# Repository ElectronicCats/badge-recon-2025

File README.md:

# REcon Badge 2025

This is the official repository of the REcon Badge 2025. Here you will find the source code for the badge, as well as the documentation and instructions to build it.

## Getting Started

Your badge comes with a pre-installed firmware, but in case you want to reprogram it, you can follow these steps:

1. Download the latest `firmware.uf2` file from the [releases](https://github.com/ElectronicCats/badge-recon-2025/releases/latest) page.

2. Connect the badge to your computer using a USB-C cable.

3. Press and hold the button on the badge while connecting it to the USB port. This will put the badge in bootloader mode.

4. Once the badge is connected, it will appear as a USB drive named `RPI-RP2`. Copy the `firmware.uf2` file to the root of the drive.

5. After copying the file, the badge will automatically reboot and start running the new firmware.

> **Note:** Sometimes you may need to press the reset button on the badge after copying the firmware file to ensure it starts correctly.

### Building the Firmware

To build the firmware from source, you will need to have [Docker](https://www.docker.com/) installed on your machine. Once you have Docker set up, you can follow these steps:

1. Clone the repository:

Using HTTPS:

```bash
git clone https://github.com/ElectronicCats/badge-recon-2025.git
```

Using SSH:

```bash
git clone git@github.com:ElectronicCats/badge-recon-2025.git
```

2. Navigate to the firmware directory:

```bash
cd badge-recon-2025/firmware
```

3. Build the firmware using Docker:

```bash
./build.sh
```

This script will create a `firmware.ino.uf2` file in the `firmware/build` directory.

> To flash the firmware to the badge, follow the same steps as mentioned in the "Getting Started" section, but use the newly built `firmware.ino.uf2` file instead of the pre-built one.

> If you find any issues, please open an issue on the GitHub repository.

## User guide

Your badge comes with an SSD1306 OLED display and 4 buttons for navigation. When you power on the badge, it will display a welcome screen and then show the main menu after you press any button.

All the available applications are listed in the following diagram:

```mermaid
flowchart TD
    Start([Power On]) --> Init[Initialize Hardware]
    Init --> Welcome[Welcome Screen]
    Welcome --> MainMenu[Main Menu]
    
    MainMenu --> Apps[Apps]
    MainMenu --> About[About Screen]
    
    Apps --> NFCMenu[NFC Menu]
    Apps --> MagspoofMenu[Magspoof Menu]
    
    %% NFC Menu items
    NFCMenu --> DetectTags[Detect Tags]
    NFCMenu --> DetectReaders[Detect Readers]
    NFCMenu --> ReadBlock[Read Block]
    NFCMenu --> WriteBlock[Write Block]
    
    %% Magspoof Menu items
    MagspoofMenu --> Emulate[Emulate]
    MagspoofMenu --> Setup[Setup]
    MagspoofMenu --> Help[Help]
    
    %% NFC operations
    DetectTags --> SetReaderMode[Set Reader Mode]
    SetReaderMode --> TagDetection{Tag Detected?}
    TagDetection -->|Yes| DisplayTagInfo[Display Tag Info]
    TagDetection -->|No| BackPressed{Back Pressed?}
    BackPressed -->|Yes| NFCMenu
    BackPressed -->|No| TagDetection
    DisplayTagInfo --> WaitForRemoval[Wait For Tag Removal]
    WaitForRemoval --> BackToMenu[Wait For Back Button]
    BackToMenu --> NFCMenu
    
    %% Magspoof operations
    Setup --> SerialPrompt[Serial Prompt for Tracks]
    SerialPrompt --> InputTracks[Input Track Data]
    InputTracks --> TracksUpdated[Tracks Updated]
    TracksUpdated --> MagspoofMenu
    
    %% Input controller
    subgraph InputControl [Input Controller]
        UpButton[Up Button]
        DownButton[Down Button]
        SelectButton[Select Button]
        BackButton[Back Button]
    end
    
    %% Easter egg
    UpButton --> KonamiCheck{Konami Code?}
    KonamiCheck -->|Yes| EasterEgg[Easter Egg hint]
    KonamiCheck -->|No| MainMenu
```

### NFC Applications

- **Read Block** and **Write Block** applications are the same as **Detect Tags**, but they perform read and read/write operations if the detected tag is a Mifare Classic tag.
- **Detect Readers** allows you to detect NFC readers by emulating a tag.

### Magspoof Application

The **Magspoof** application allows you to emulate a magnetic stripe card.

- You can set up the tracks by entering the data through the serial prompt, use 9600 baud rate to communicate with the badge.
- The **Emulate** option allows you to emulate the magnetic stripe card with the configured tracks.

### Easter Egg

You can get a hint about the Easter egg by pressing the Konami code while the badge shows the REcon logo. The Konami code is:

```
Up, Up, Down, Down, Left, Right, Left, Right
```

## License

Electronic Cats invests time and resources providing this open source design, please support Electronic Cats and open-source hardware by purchasing products from Electronic Cats!

Designed by Electronic Cats.

Firmware released under an GNU AGPL v3.0 license. See the LICENSE file for more information.

Hardware released under an CERN Open Hardware Licence v1.2. See the LICENSE_HARDWARE file for more information.

Electronic Cats is a registered trademark, please do not use if you sell these PCBs.

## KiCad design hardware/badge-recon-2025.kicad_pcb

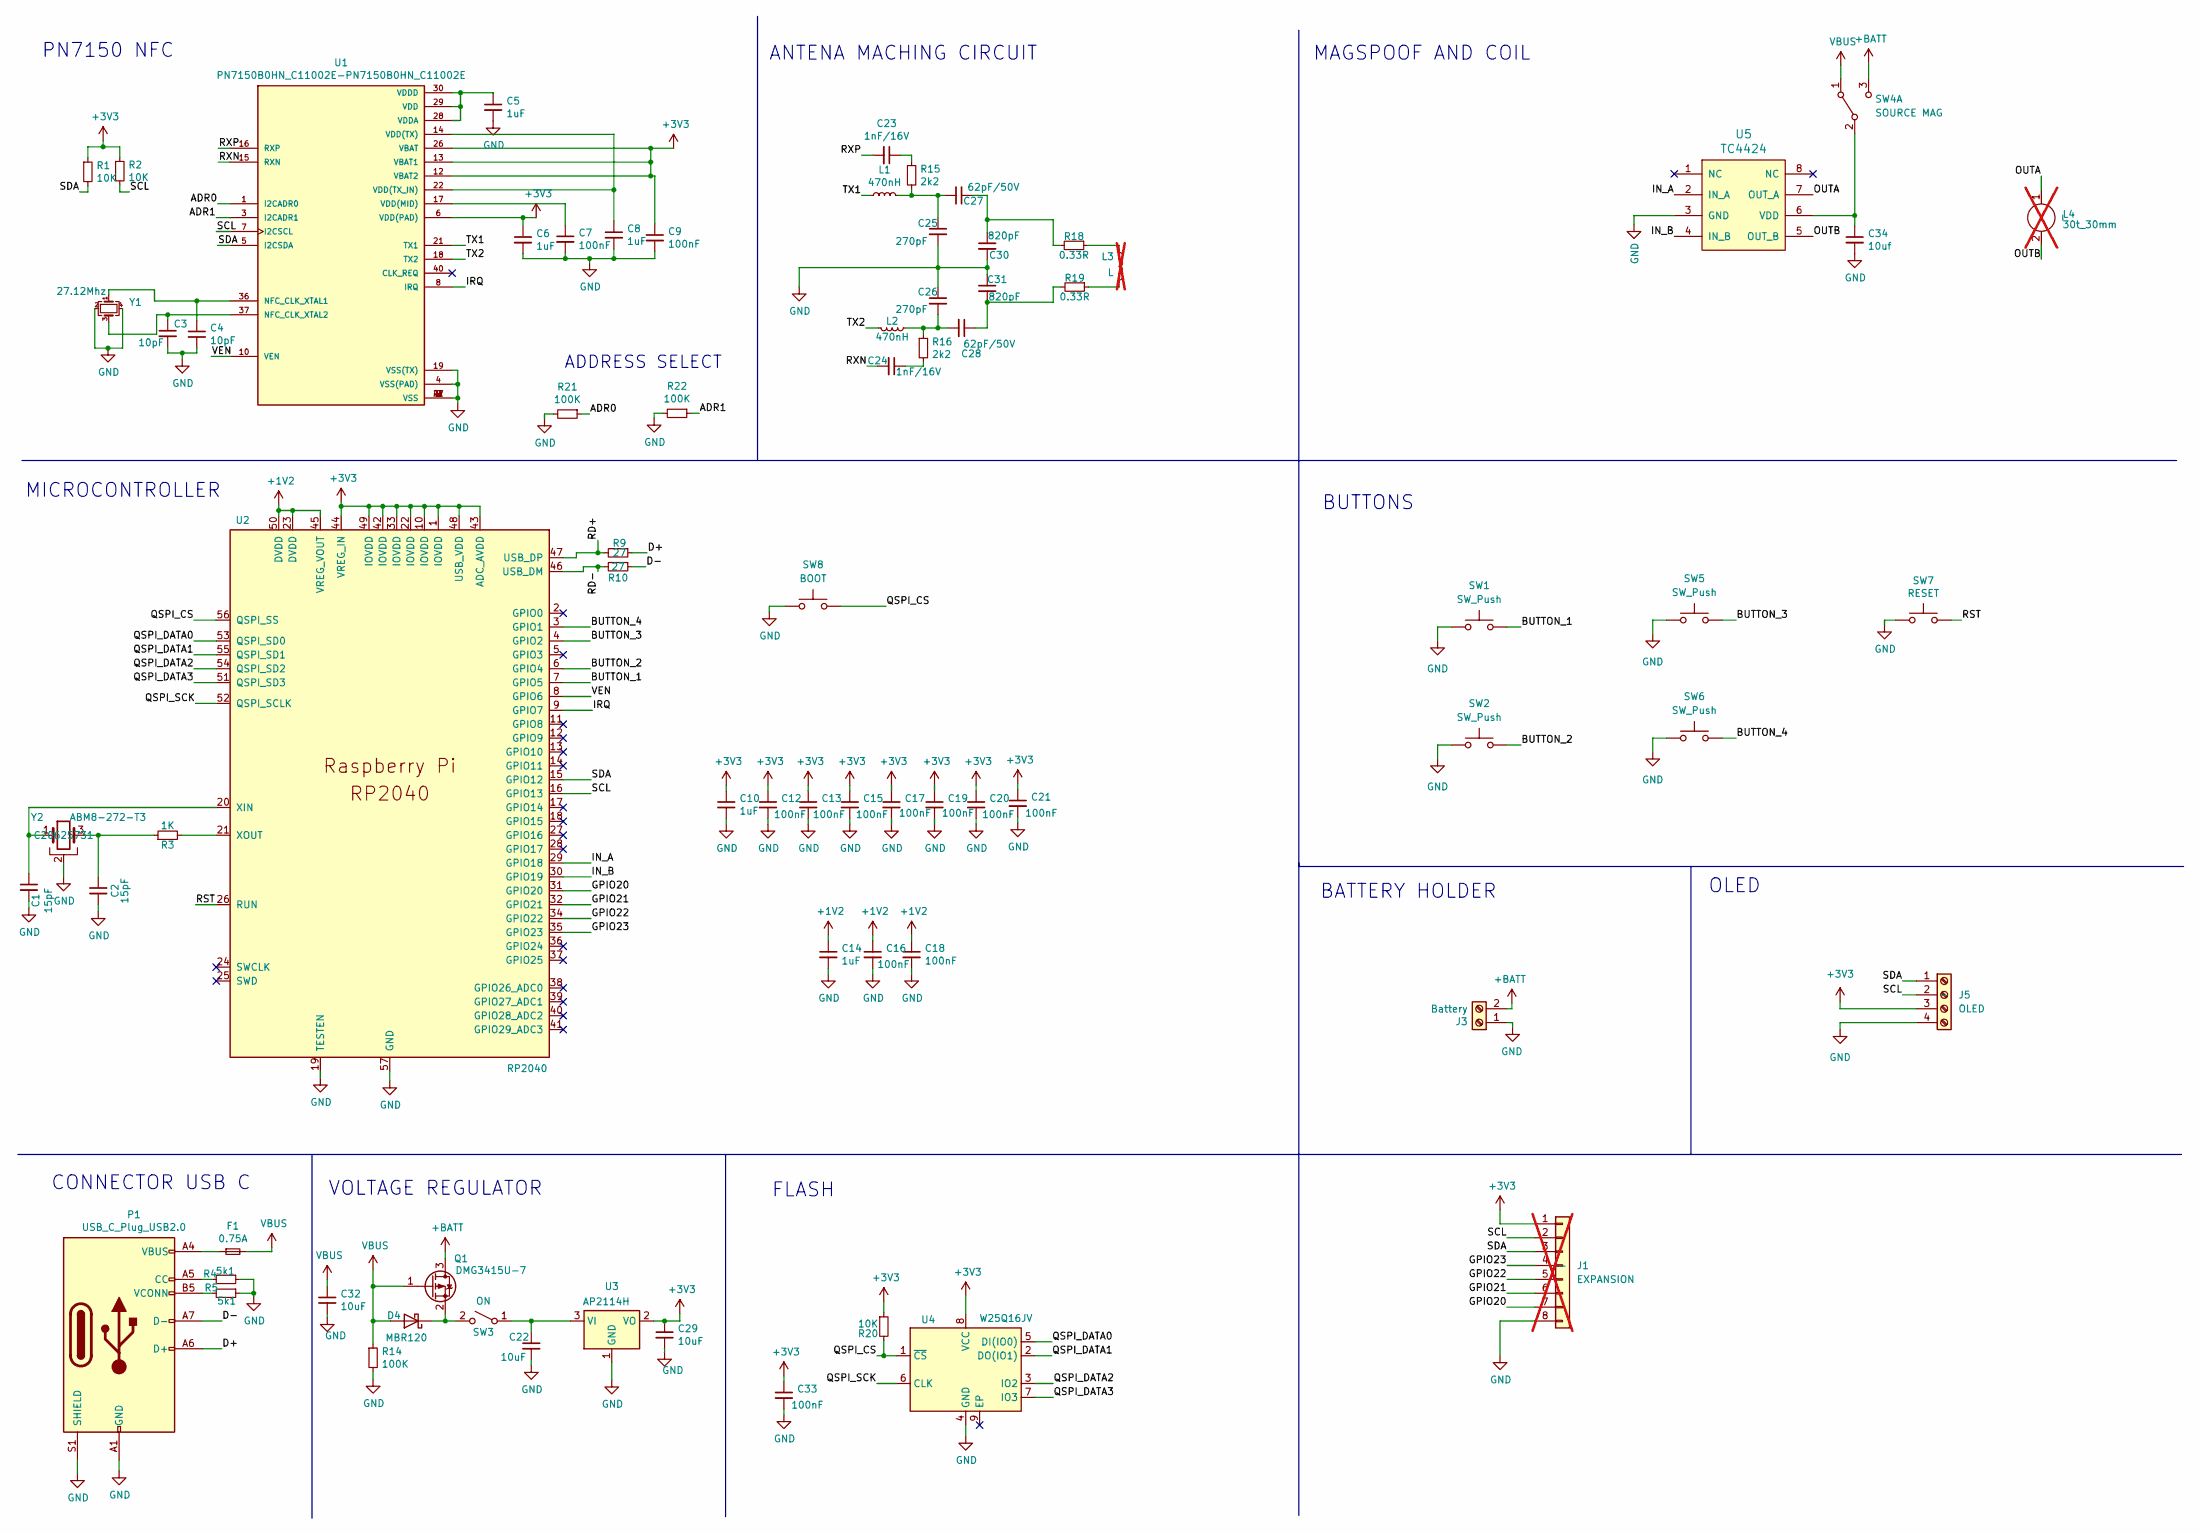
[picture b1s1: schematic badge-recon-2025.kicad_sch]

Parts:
C1, C2: 15pF; C_0603_1608Metric; LCSC# C1644
C3, C4: 10pF; C_0603_1608Metric; LCSC# C106245
C5, C6, C8, C10, C14: 1uF; C_0603_1608Metric; LCSC# C15849
C7, C9, C12, C13, C15, C16, C17, C18, C19, C20, C21, C33: 100nF; C_0603_1608Metric; LCSC# C282519
C22, C29, C32: 10uF; C_0603_1608Metric; LCSC# C85713
C23, C24: 1nF/16V; C_0603_1608Metric; LCSC# C519507
C25, C26: 270pF; C_0603_1608Metric; LCSC# C107046
C27, C28: 62pF/50V; C_0603_1608Metric; LCSC# C282073
C30, C31: 820pF; C_0603_1608Metric; LCSC# C107057
C34: 10uf; C_0603_1608Metric; LCSC# C96446
D4: MBR120; D_SOD-123F; LCSC# C130880
F1: 0.75A; Fuse_1812_4532Metric; LCSC# C3107
J1: EXPANSION; PinHeader_1x08_P2.54mm_Vertical; not fitted
J3: Battery; BAT-TH_BH-AAA-A1AJ024; LCSC# C5290193
J5: OLED; Display OLED 128 x32
L1, L2: 470nH; L_0603_1608Metric_Pad1.05x0.95mm_HandSolder; LCSC# C2044483
L3: L; NFC_Antenna_4T_Crossover_Final; not fitted
L4: 30t_30mm; Coil_30t_30mm_0.2_0.2_0.6_0.3; not fitted
P1: USB_C_Plug_USB2.0; C393939; LCSC# C393939
Q1: DMG3415U-7; SOT-23; LCSC# C96616
R1, R2, R20: 10K; R_0603_1608Metric; LCSC# C2930027
R3: 1K; R_0603_1608Metric; LCSC# C112433
R4, R5: 5k1; R_0603_1608Metric; LCSC# C23186
R9, R10: 27; R_0603_1608Metric; LCSC# C403464
R14, R21, R22: 100K; R_0603_1608Metric; LCSC# C15458
R15, R16: 2k2; R_0603_1608Metric; LCSC# C113303
R18, R19: 0.33R; R_0603_1608Metric; LCSC# C2934252
SW1, SW2, SW5, SW6: SW_Push; SW_SPST_TL3342; LCSC# C318889
SW3: ON; MSK12C02; LCSC# C431540
SW4: SOURCE MAG; JS202011CQN; LCSC# C5149820
SW7: RESET; SW_SPST_TL3342; LCSC# C318889
SW8: BOOT; SW_SPST_TL3342; LCSC# C318889
U1: PN7150B0HN_C11002E-PN7150B0HN_C11002E; QFN-40-1EP_6x6mm_P0.5mm_EP4.6x4.6mm; LCSC# C702907
U2: RP2040; RP2040-QFN-56; LCSC# C2040
U3: AP2114H; SOT-223-3_TabPin2; LCSC# C150716
U4: W25Q16JV; SOIC-8_5.3x5.3mm_P1.27mm; LCSC# C82317
U5: TC4424; SOIC-8_3.9x4.9mm_P1.27mm; LCSC# C7498963
Y1: 27.12Mhz; Crystal_SMD_2016-4Pin_2.0x1.6mm; LCSC# C338245
Y2: ABM8-272-T3; Crystal_SMD_Abracon_ABM8G-4Pin_3.2x2.5mm; LCSC# C20625731

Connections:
+1V2: C14.1, C16.1, C18.1, U2.23 (DVDD), U2.45 (VREG_VOUT), U2.50 (DVDD)
+3V3: C6.1, C9.1, C10.1, C12.1, C13.1, C15.1, C17.1, C19.1, C20.1, C21.1, C29.1, C33.1, J1.1, J5.3, R1.1, R2.1, R20.1, U1.6 (VDD(PAD)), U1.12 (VBAT2), U1.13 (VBAT1), U1.26 (VBAT), U2.1 (IOVDD), U2.10 (IOVDD), U2.22 (IOVDD), U2.33 (IOVDD), U2.42 (IOVDD), U2.43 (ADC_AVDD), U2.44 (VREG_IN), U2.48 (USB_VDD), U2.49 (IOVDD), U3.2 (VO), U4.8 (VCC)
+BATT: J3.2, Q1.3 (D), SW4.3 (C)
/ADR0: R21.1, U1.1 (I2CADR0)
/ADR1: R22.1, U1.3 (I2CADR1)
/BUTTON_1: SW1.2, U2.7 (GPIO5)
/BUTTON_2: SW2.2, U2.6 (GPIO4)
/BUTTON_3: SW5.2, U2.4 (GPIO2)
/BUTTON_4: SW6.2, U2.3 (GPIO1)
/D+: P1.A6 (D+), R9.1
/D-: P1.A7 (D-), R10.1
/GPIO20: J1.7, U2.31 (GPIO20)
/GPIO21: J1.6, U2.32 (GPIO21)
/GPIO22: J1.5, U2.34 (GPIO22)
/GPIO23: J1.4, U2.35 (GPIO23)
/IN_A: U2.29 (GPIO18), U5.2 (IN_A)
/IN_B: U2.30 (GPIO19), U5.4 (IN_B)
/IRQ: U1.8 (IRQ), U2.9 (GPIO7)
/OUTA: L4.1, U5.7 (OUT_A)
/OUTB: L4.2, U5.5 (OUT_B)
/QSPI_CS: R20.2, SW8.2, U2.56 (QSPI_SS), U4.1 (~CS)
/QSPI_DATA0: U2.53 (QSPI_SD0), U4.5 (DI(IO0))
/QSPI_DATA1: U2.55 (QSPI_SD1), U4.2 (DO(IO1))
/QSPI_DATA2: U2.54 (QSPI_SD2), U4.3 (IO2)
/QSPI_DATA3: U2.51 (QSPI_SD3), U4.7 (IO3)
/QSPI_SCK: U2.52 (QSPI_SCLK), U4.6 (CLK)
/RD+: R9.2, U2.47 (USB_DP)
/RD-: R10.2, U2.46 (USB_DM)
/RST: SW7.2, U2.26 (RUN)
/RXN: C24.2, U1.15 (RXN)
/RXP: C23.2, U1.16 (RXP)
/SCL: J1.2, J5.2, R2.2, U1.7 (I2CSCL), U2.16 (GPIO13)
/SDA: J1.3, J5.1, R1.2, U1.5 (I2CSDA), U2.15 (GPIO12)
/TX1: L1.1, U1.21 (TX1)
/TX2: L2.2, U1.18 (TX2)
/VEN: U1.10 (VEN), U2.8 (GPIO6)
GND: C1.2, C2.2, C3.2, C4.2, C5.2, C6.2, C7.2, C8.2, C9.2, C10.2, C12.2, C13.2, C14.2, C15.2, C16.2, C17.2, C18.2, C19.2, C20.2, C21.2, C22.2, C25.2, C26.1, C29.2, C30.2, C31.1, C32.2, C33.2, C34.2, J1.8, J3.1, J5.4, P1.A1 (GND), P1.A12 (GND), P1.B1 (GND), P1.B12 (GND), P1.S1 (SHIELD), R4.1, R5.1, R14.2, R21.2, R22.2, SW1.1, SW2.1, SW5.1, SW6.1, SW7.1, SW8.1, U1.2 (VSS), U1.4 (VSS(PAD)), U1.9 (VSS), U1.19 (VSS(TX)), U1.27 (VSS), U1.41 (VSS), U2.19 (TESTEN), U2.57 (GND), U3.1 (GND), U4.4 (GND), U5.3 (GND), Y1.2, Y1.4, Y2.2
unnamed: C2.1, R3.1, Y2.3
unnamed: C23.1, R15.1
unnamed: C24.1, R16.2
unnamed: C25.1, C27.2, L1.2, R15.2
unnamed: C26.2, C28.2, L2.1, R16.1
unnamed: C27.1, C30.1, R18.2
unnamed: C28.1, C31.2, R19.2
unnamed: D4.1 (K), Q1.2 (S), SW3.2 (B)
unnamed: F1.1, P1.A4 (VBUS), P1.A9 (VBUS), P1.B4 (VBUS), P1.B9 (VBUS)
unnamed: L3.1, R18.1
unnamed: L3.2, R19.1
unnamed: P1.A5 (CC), R4.2
unnamed: P1.B5 (VCONN), R5.2
unnamed: C22.1, SW3.1 (A), U3.3 (VI)
unnamed: C34.1, SW4.2 (B), U5.6 (VDD)
unnamed: C4.1, U1.36 (NFC_CLK_XTAL1), Y1.1
unnamed: C3.1, U1.37 (NFC_CLK_XTAL2), Y1.3
unnamed: C7.1, U1.17 (VDD(MID))
unnamed: C8.1, U1.14 (VDD(TX)), U1.22 (VDD(TX_IN))
unnamed: C5.1, U1.28 (VDDA), U1.29 (VDD), U1.30 (VDDD)
unnamed: C1.1, U2.20 (XIN), Y2.1
unnamed: R3.2, U2.21 (XOUT)
VBUS: C32.1, D4.2 (A), F1.2, Q1.1 (G), R14.1, SW4.1 (A)

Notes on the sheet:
ANTENA MACHING CIRCUIT
CONNECTOR USB C
PN7150 NFC
BATTERY HOLDER
BUTTONS
MAGSPOOF AND COIL
MICROCONTROLLER
VOLTAGE REGULATOR
FLASH
OLED
ADDRESS SELECT

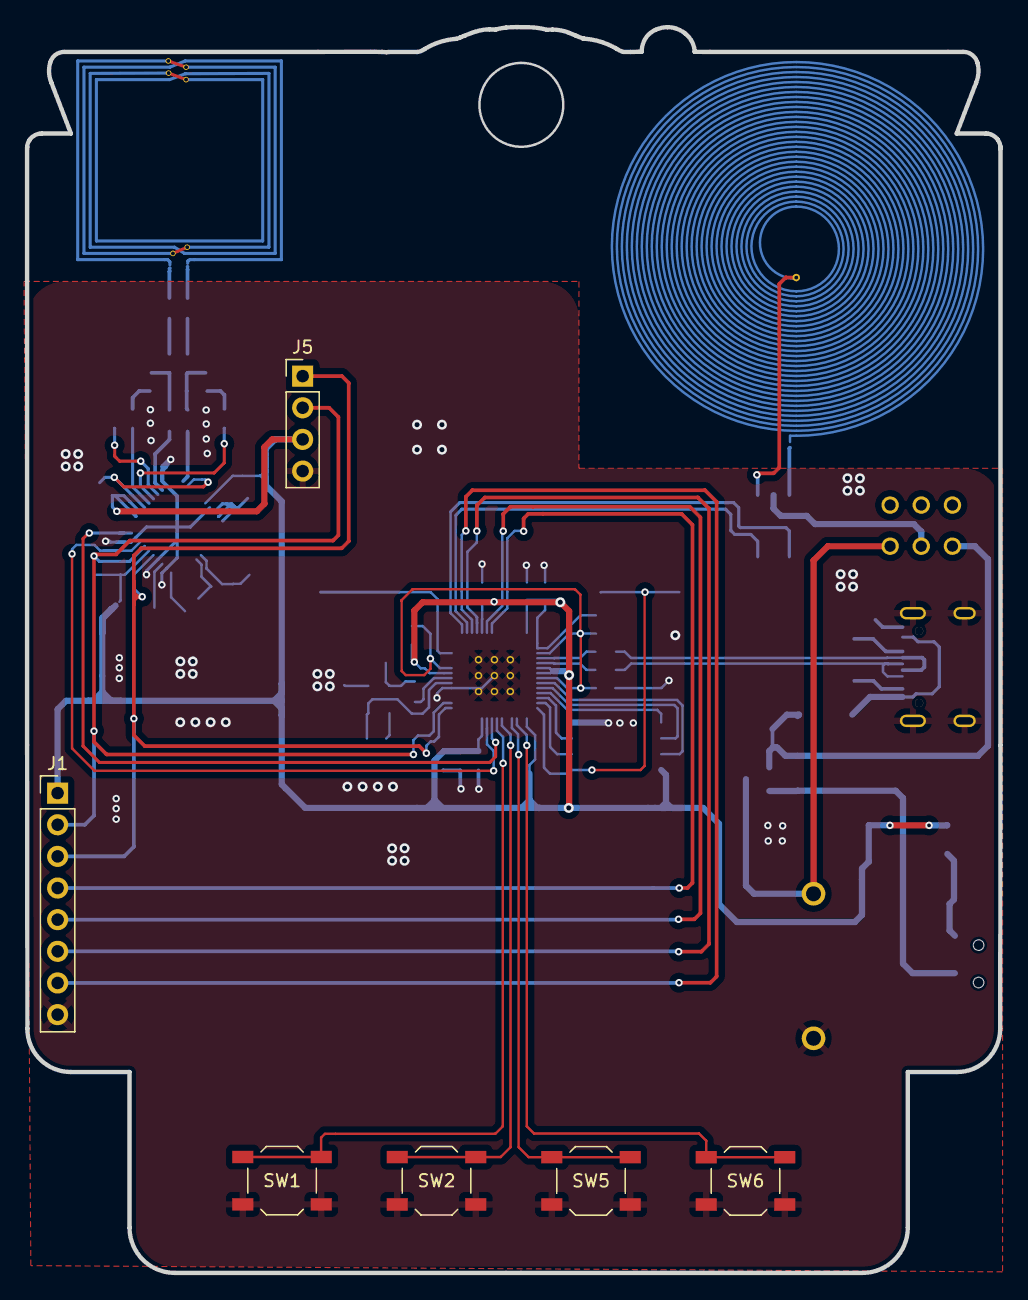
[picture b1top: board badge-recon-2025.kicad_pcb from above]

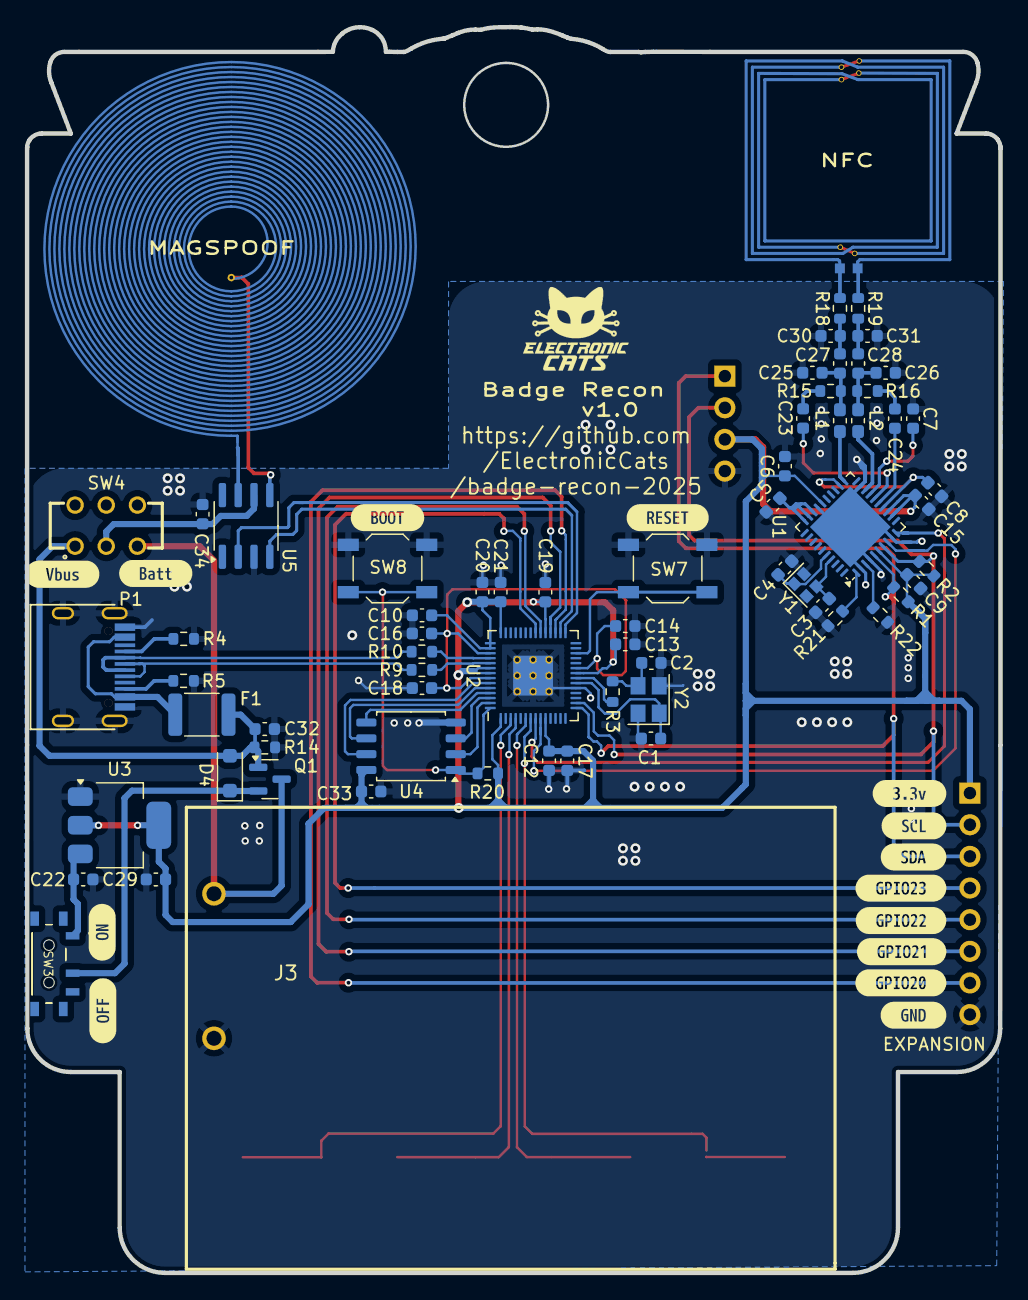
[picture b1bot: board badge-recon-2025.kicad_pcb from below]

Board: 2 copper layers, 78.1 x 100.0 mm, 88 parts (82 on the bottom side), 60 nets.

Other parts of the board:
kibuzzard-6806AEF7: G***; kibuzzard-6806AEF7
kibuzzard-6806AF2D: G***; kibuzzard-6806AF2D
kibuzzard-6806AF6E: G***; kibuzzard-6806AF6E
kibuzzard-6806AF7F: G***; kibuzzard-6806AF7F
kibuzzard-6806AF29: G***; kibuzzard-6806AF29
kibuzzard-6806AF43: G***; kibuzzard-6806AF43
kibuzzard-6806AF94: G***; kibuzzard-6806AF94
kibuzzard-6806AFC6: G***; kibuzzard-6806AFC6
kibuzzard-6806B2E8: G***; kibuzzard-6806B2E8
kibuzzard-6806B2F9: G***; kibuzzard-6806B2F9
kibuzzard-6814FFA5: G***; kibuzzard-6814FFA5
kibuzzard-6814FFAA: G***; kibuzzard-6814FFAA
kibuzzard-6815045B: G***; kibuzzard-6815045B
kibuzzard-68150444: G***; kibuzzard-68150444

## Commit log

2025-04-07 feat(hw): add kicad project & add components in schematic
2025-04-07 feat(hw): add oled in schematic
2025-04-10 feat(Hw):Update_BOM
2025-04-11 feat(Hw):Init_Floorplan
2025-04-14 feat(Hw):Update_Floorplan
2025-04-16 feat(Hw): add antenna missing matching circuit
2025-04-16 feat(Hw): add ideal matching circuit
2025-04-18 Feat(Hw): floorplan added
2025-04-20 feat(Hw): update part numbers for JLCPCB assembly
2025-04-22 feat(Hw): add expansor, 0 unconnected, missing pn7150 crystal
2025-04-23 feat(Hw): update part numbers for jlcpcb
2025-04-23 fix(Hw): set component as dnp & move routes
2025-04-23 fix(Hw): fix traces
2025-05-02 feat(Hw):Update_Labels
2025-05-07 chore: add firmware template
2025-05-07 docs: update author and date on firmware header docs
2025-05-07 chore: move firmware gitignore to global gitignore
2025-05-07 chore: add build path
2025-05-07 refactor: project structure
2025-05-07 fix: ic2 and pn7150 pins
2025-05-11 chore: delete build directory
2025-05-11 feat: add buttons integration
2025-05-12 feat: add menus system
2025-05-12 feat: add recon logo at startup
2025-05-12 feat: integrate detect tags on the screen
2025-05-12 feat: add detect readers
2025-05-12 fix: set reader/writer mode for detect tags
2025-05-13 feat: add ndef read support
2025-05-14 feat: display record info on terminal
2025-05-14 refactor: menu controller into main ino file
2025-05-19 fix: detect tags do not work
2025-05-19 feat: remove detect readers animation
2025-05-20 feat: add magspoof
2025-05-20 feat: display remove tag
2025-05-20 feat: add read mifare block
2025-05-20 feat: add default magspoof tracks
2025-05-20 feat: let user to add custom tracks
2025-05-21 fix(fw): detect readers
2025-05-23 feat: show logo until user presses a any button
2025-05-23 feat: add reboot counter
2025-05-23 refactor: set chip mode
2025-05-23 feat: add mifare write
2025-05-26 feat: add easter egg
2025-05-26 feat: add konami code
2025-05-26 feat: add dockerfile and docker compose
2025-05-26 feat: remove set chip warning
    - Remove useless comments
    - Remove useless prints
2025-05-26 chore: rename output dir
2025-05-26 fix: write block validation statements
2025-05-26 docs: add getting started
2025-05-26 chore: remove duplicated library
2025-05-26 chore: add selinux compatibility
2025-05-27 docs: add user guide
2025-05-27 chore: add licenses
2025-05-27 docs: fix typo
